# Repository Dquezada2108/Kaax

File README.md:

# Kaax
Hi there! Here you may find the CAD files, code and other resources that we have developed to create Kaax, our robot desegned to remove sargasso off the coast of the Mexican Caribean. Feel free to explore and discover what we have created.

This is a project I am passionate about that incorporates a central claw that uses servos to remove sargasso from the water. It is destined to cleaning the sea. We were inspired by the huge amount of this seaweed that constalty arrives to our beaches in the Mexican Caribbean. We had the knowledge necessary to pull this project off. And also, this can be the base for a diiversity of other acquatic projects like a rescue bot and an oil spill cleaner. This is the future and we as citizens have the responsability to do something, our part, to solve the problems we encounter. Many times while being on vacation sargasso ended up ruining the experience, and I could see how many people spent a lot of time and effort removing it, long hours under the sun.

# 3D Model V1

# 3D Model V2

# 3D Model V3

# Wiring

# BOM
| Component | Purpose | Qty | Unit | Total | Source |
|---|---|---:|---:|---:|---|
| Jumper wires (assorted) | Connect sensors and motors | 1 | $8.59 | $8.59 | [Amazon](https://www.amazon.com/IZOKEE-cables-puente-tabla-soldadura/dp/B08151TQHG) |
| MG995 servos (4-pack) | Claw mechanism | 1 | $17.98 | $17.98 | [Amazon](https://www.amazon.com/-/es/Servo-MG995-Metal-Inteligente-Helic%C3%B3ptero/dp/B07NQJ1VZ2) |
| USB webcam | Computer vision | 1 | $15.99 | $15.99 | [Amazon](https://www.amazon.com/-/es/Lusinx-computadora-correcci%C3%B3n-autom%C3%A1tica-privacidad/dp/B0F2FLKZWQ) |
| MPU-9250 IMU | Navigation (accel + gyro + mag) | 1 | $23.49 | $23.49 | [Amazon](https://www.amazon.com/HiLetgo-giroscopio-aceleraci%C3%B3n-acelerador-magnet%C3%B3metro/dp/B01I1J0Z7Y) |
| Ovonic 4S LiPo battery | Main power (motors) | 2 | $34.99 | $69.98 | [Amazon](https://www.amazon.com/OVONIC-100C-conector-Quadcopter-paquetes/dp/B0821YX6JB) |
| Apisqueen U5 thruster | Propulsion | 2 | $99.69 | $199.38 | [Amazon](https://www.amazon.com/-/es/Subacu%C3%A1tico-ESC-Bidireccional-100A-CCW/dp/B0D69YX31K) |
| Raspberry Pi 5 (16 GB) | Main computer | 1 | $339.99 | $339.99 | [Amazon](https://www.amazon.com/s?k=raspberry+pi+5+16+GB+ram) |
| **Total** | | | | **$675.40** | |

# PCB
Here is the schematic of the pcb as well as some images of the design and how it should look. Keep in mind it only uses male and female connectors to lower the manufacturing costs.

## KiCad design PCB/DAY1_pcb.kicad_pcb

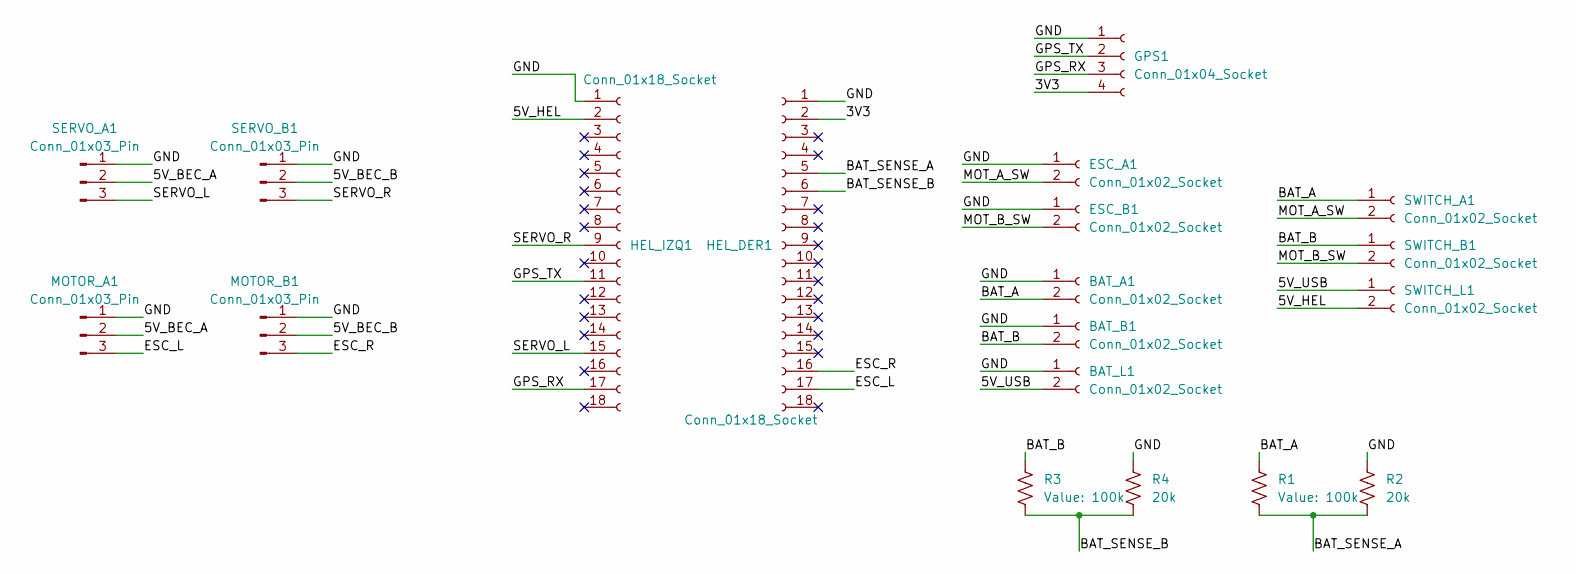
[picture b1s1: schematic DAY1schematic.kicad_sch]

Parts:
BAT_A1: Conn_01x02_Socket; AMASS_XT60-M_1x02_P7.20mm_Vertical
BAT_B1: Conn_01x02_Socket; AMASS_XT60-M_1x02_P7.20mm_Vertical
BAT_L1: Conn_01x02_Socket; AMASS_XT30U-F_1x02_P5.0mm_Vertical
ESC_A1: Conn_01x02_Socket; AMASS_XT60-F_1x02_P7.20mm_Vertical
ESC_B1: Conn_01x02_Socket; AMASS_XT60-F_1x02_P7.20mm_Vertical
GPS1: Conn_01x04_Socket; PinSocket_1x04_P2.54mm_Vertical
HEL_DER1: Conn_01x18_Socket; PinSocket_1x18_P2.54mm_Vertical
HEL_IZQ1: Conn_01x18_Socket; PinSocket_1x18_P2.54mm_Vertical
MOTOR_A1: Conn_01x03_Pin; PinHeader_1x03_P2.54mm_Vertical
MOTOR_B1: Conn_01x03_Pin; PinHeader_1x03_P2.54mm_Vertical
R1, R3: 100k; R_Axial_DIN0207_L6.3mm_D2.5mm_P10.16mm_Horizontal
R2, R4: 20k; R_Axial_DIN0207_L6.3mm_D2.5mm_P10.16mm_Horizontal
SERVO_A1: Conn_01x03_Pin; PinHeader_1x03_P2.54mm_Vertical
SERVO_B1: Conn_01x03_Pin; PinHeader_1x03_P2.54mm_Vertical
SWITCH_A1: Conn_01x02_Socket; AMASS_XT30U-F_1x02_P5.0mm_Vertical
SWITCH_B1: Conn_01x02_Socket; AMASS_XT30U-F_1x02_P5.0mm_Vertical
SWITCH_L1: Conn_01x02_Socket; AMASS_XT30U-F_1x02_P5.0mm_Vertical

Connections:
/3V3: GPS1.4, HEL_DER1.2
/5V_BEC_A: MOTOR_A1.2, SERVO_A1.2
/5V_BEC_B: MOTOR_B1.2, SERVO_B1.2
/5V_HEL: HEL_IZQ1.2, SWITCH_L1.2
/5V_USB: BAT_L1.2, SWITCH_L1.1
/BAT_A: BAT_A1.2, R1.1, SWITCH_A1.1
/BAT_B: BAT_B1.2, R3.1, SWITCH_B1.1
/BAT_SENSE_A: HEL_DER1.5, R1.2, R2.2
/BAT_SENSE_B: HEL_DER1.6, R3.2, R4.2
/ESC_L: HEL_DER1.17, MOTOR_A1.3
/ESC_R: HEL_DER1.16, MOTOR_B1.3
/GND: BAT_A1.1, BAT_B1.1, BAT_L1.1, ESC_A1.1, ESC_B1.1, GPS1.1, HEL_DER1.1, HEL_IZQ1.1, MOTOR_A1.1, MOTOR_B1.1, R2.1, R4.1, SERVO_A1.1, SERVO_B1.1
/GPS_RX: GPS1.3, HEL_IZQ1.17
/GPS_TX: GPS1.2, HEL_IZQ1.11
/MOT_A_SW: ESC_A1.2, SWITCH_A1.2
/MOT_B_SW: ESC_B1.2, SWITCH_B1.2
/SERVO_L: HEL_IZQ1.15, SERVO_A1.3
/SERVO_R: HEL_IZQ1.9, SERVO_B1.3

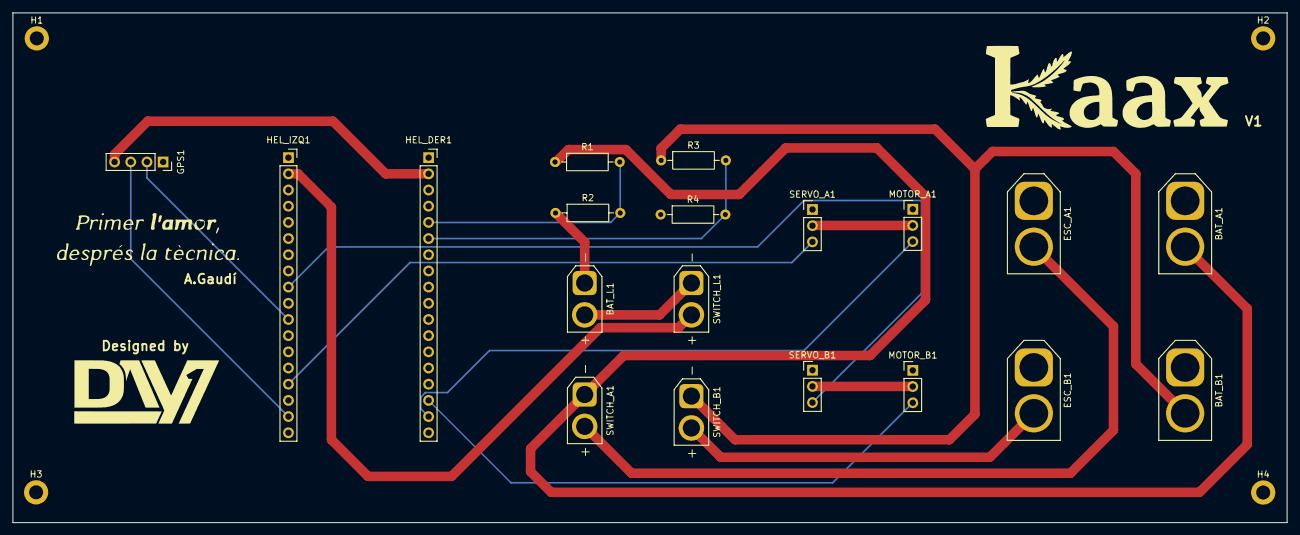
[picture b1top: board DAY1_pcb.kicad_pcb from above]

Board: 2 copper layers, 200.0 x 80.0 mm, 26 parts (0 on the bottom side), 18 nets.

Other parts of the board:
A.Gaudí: LOGO; Gaudi
Designed by: LOGO; DAY1
H1, H2, H3, H4: MountingHole_2.2mm_M2_DIN965_Pad
V1: LOGO; Kaax

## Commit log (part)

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2026-02-17 Revise README to enhance project overview
    Updated project description for clarity and detail.
2026-02-17 Add image processing script for plant detection
2026-04-16 Create control
2026-05-05 Add CAD design portfolio for robotics and engineering
    This document outlines a CAD design portfolio focusing on robotics and product engineering, detailing various design projects, objectives, engineering focus, and key takeaways.
2026-05-05 Create Links
2026-05-05 Update Links
2026-05-05 Add documentation for Kaax ROV Controller
    Added detailed documentation for the Kaax Raspberry Pi ROV Controller, including sections on connectivity, web interface, hardware control, computer vision, sensors, control system, data analytics, a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
2026-05-05 Create control_v1
2026-05-05 Rename Full Robot CAD - STEP.step to Full Robot CAD.step
2026-05-05 Create BOM
2026-05-05 Create hola
2026-05-05 Add initial README with project explanation
2026-05-19 Rename Full Robot CAD.step to Full CAD_v2.step
2026-05-19 Rename Full CAD_v2.step to Full CAD_v1.step
2026-06-25 Create PCB
2026-06-25 Moved files and created PCB folder
2026-06-29 Fix PCB header formatting in README.md
    Updated PCB section header and adjusted formatting.
